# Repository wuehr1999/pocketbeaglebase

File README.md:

# pocketbeaglebase

Add lots of useful features to Your PocketBeagle.

## Features

* Input voltage range: 5 - 28V
* 10/100 Base-T/TX ethernet interface
* 2 USB 2.0 connectors
* RS-232 interface
* CAN interface
* Qwiic connectors: 2 x UART, PRU1 UART, ISC1
* SPI header
* GPIO header

## Connectors

### SPI1 header (P8)

| Pin | Function |
|-----|----------|
| 1 | MISO |
| 2 | 3V3 |
| 3 | SCK |
| 4 | MOSI |
| 5 | CS |
| 6 | GND |

### GPIO header (P4)

| Pin | Function |
|-----|----------|
| 1 | AIN7 |
| 2 | AIN5 |
| 3 | PRU0.5 |
| 4 | IO45 |
| 5 | PRU0.3 |
| 6 | PRU0.2 |
| 7 | IO48 |
| 8 | PRU0.6 |
| 9 | IO64 |
| 10 | IO46 |
| 11 | IO65 |
| 12 | IO27 |
| 13 | IO52 |
| 14 | IO47 |
| 15 | IO60 |
| 16 | IO57 |
| 17 | IO58 |
| 18 | IO23 |
| 19 | IO59 |
| 20 | PWM0A |
| 21 | PWM0B |
| 22 | 3V3 |
| 23 | PRU1.10 |
| 24 | IO26 |
| 25 | PRU0.1 |
| 26 | PRU0.4 |
| 27 | PRU0.7 |
| 28 | AIN4 |
| 29 | NC |
| 30 | AIN3 |
| 31 | NC |
| 32 | AIN2 |
| 33 | AIN1 |
| 34 | IO20 |
| 35 | AIN0 | 
| 36 | VRef+ |
| 37 | VRef- |
| 38 | IO89 |
| 39 | AIN6 |
| 40 | GND |

### RS-232 (UART 0)

| Pin | Function |
|-----|----------|
| 1 | TX |
| 2 | RX |
| 3 | GND |

### CAN (CAN 0)

| Pin | Function |
|-----|----------|
| 1 | CANH |
| 2 | CANL |
| 3 | GND |

The termination can be enabled by closing solder jumper P9 on the bottom of the board.

### UART2, UART4, UARTPRU1 over Qwiic (P3, P5, P6)

| Pin | Function |
|-----|----------|
| 1 | GND |
| 2 | 3v3 |
| 3 | TX |
| 4 | RX |

### I2C1 over Qwiic (P7)

| Pin | Function |
|-----|----------|
| 1 | GND |
| 2 | 3v3 |
| 3 | SDA |
| 4 | SCL |

## PCB

### Toplayer

### Bottomlayer

## Resources

### Manuals

* PocketBeagle System Reference Manual: https://github.com/beagleboard/pocketbeagle/wiki/System-Reference-Manual
* BeagleBone PRU Cookbook: http://beagleboard.org/static/prucookbook/

### Datasheets

* http://ww1.microchip.com/downloads/en/devicedoc/00002306a.pdf
* https://octavosystems.com/docs/osd335x-sm-datasheet/
* https://www.ti.com/lit/ds/symlink/sn65hvd230.pdf?HQS=dis-dk-null-digikeymode-dsf-pf-null-wwe&ts=1609524456800
* https://datasheets.maximintegrated.com/en/ds/MAX3224-MAX3245.pdf
* https://www.ti.com/lit/ds/symlink/tps54335-2a.pdf?ts=1609516162103&ref_url=https%253A%252F%252Fwww.google.com%252F
* http://ww1.microchip.com/downloads/en/devicedoc/21712b.pdf
* https://cdn-reichelt.de/documents/datenblatt/C100/M100_T1D_33E4G_DB_DE.pdf

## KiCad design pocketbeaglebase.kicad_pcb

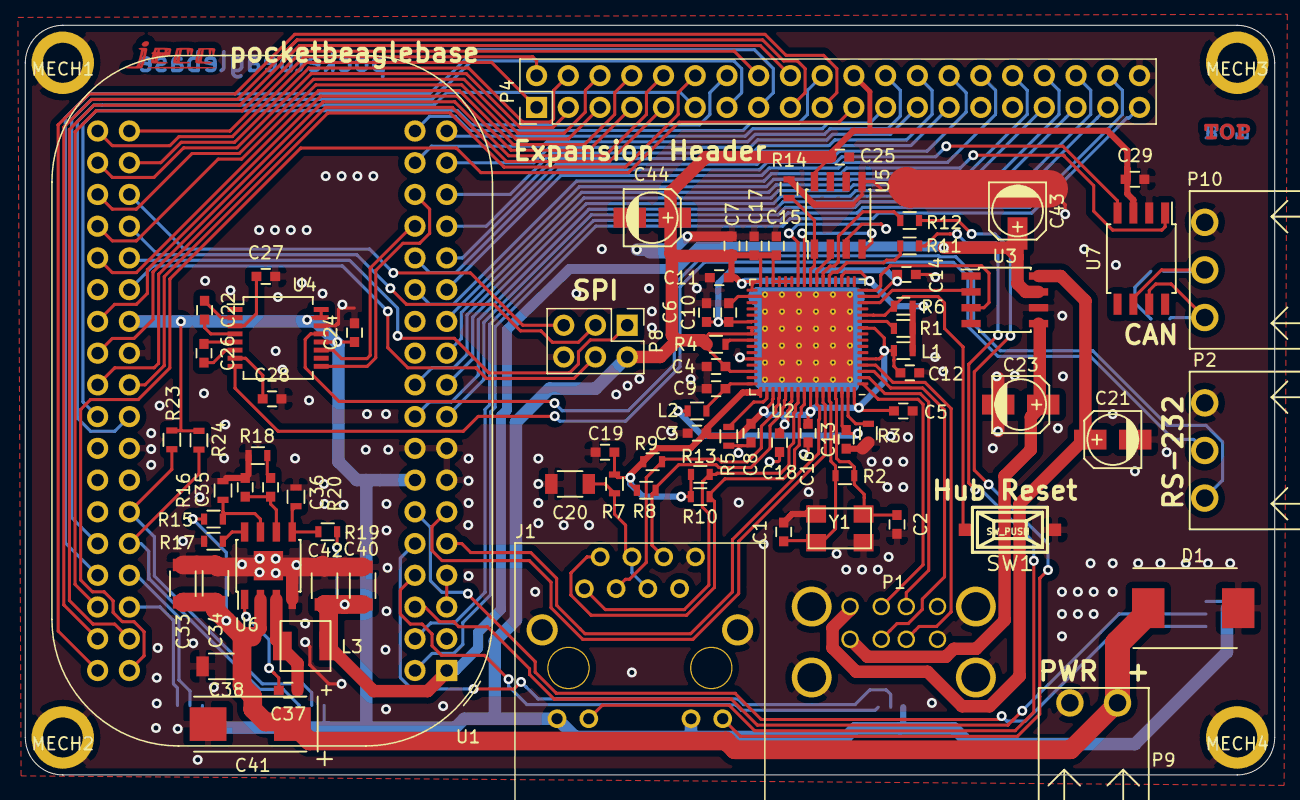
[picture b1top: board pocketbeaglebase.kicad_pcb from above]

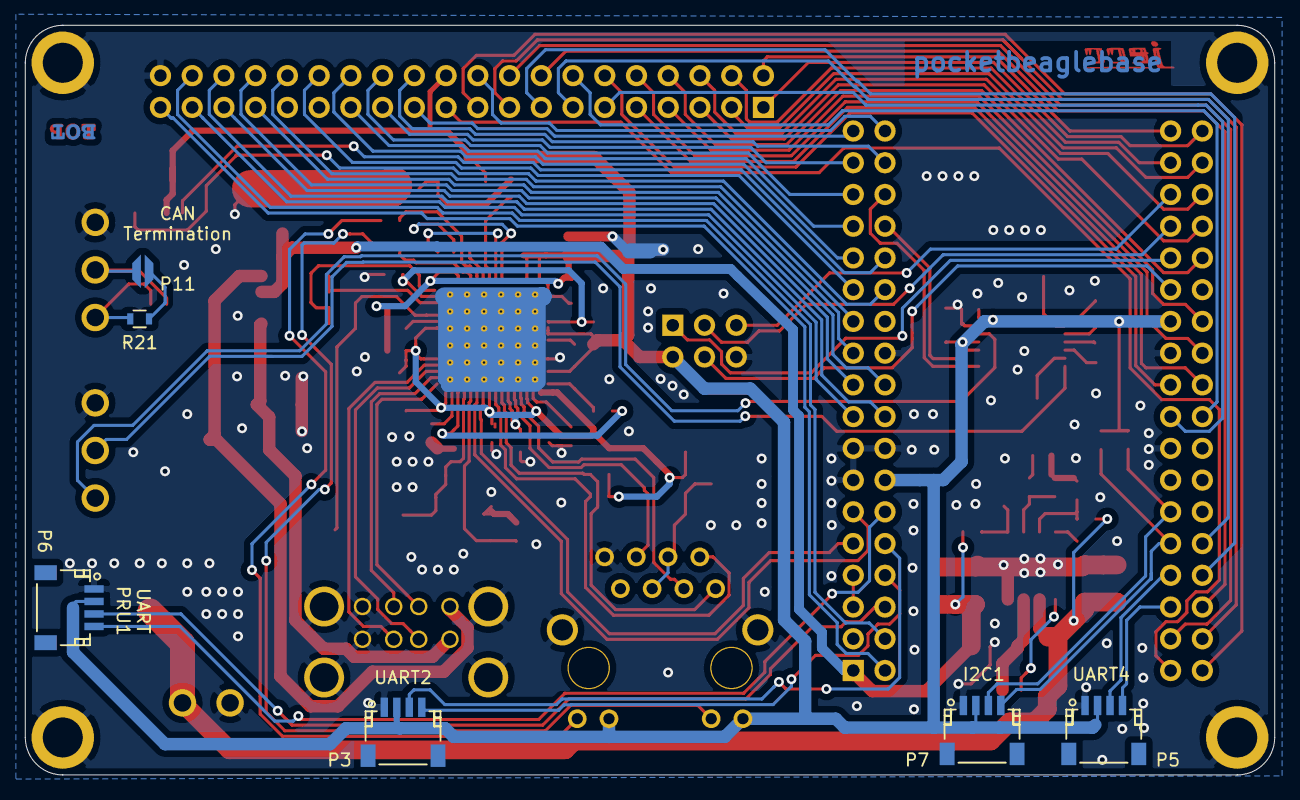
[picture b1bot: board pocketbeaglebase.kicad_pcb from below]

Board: 2 copper layers, 100.0 x 60.0 mm, 95 parts (6 on the bottom side), 109 nets.

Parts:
C1, C2: 330pF; C_0603
C3, C4, C5, C7, C8, C10, C11, C12, C14, C15, C16, C17, C18, C19, C25, C29, C37: 100nF; C_0603
C6: 4.7uF; C_0603
C9, C13, C26, C27, C28: 1uF; C_0603
C20: 22nF; C_1206
C21, C23, C43, C44: 10uF; c_elec_4x4.5
C22, C24: 220nF; C_0603
C33, C34: 4.7uF 50V; C_1206
C35: 120pF; C_0603
C36: 12nF; C_0603
C38: 100nF; C_1206
C40, C42: 22uF; C_1206
C41: 47uF; TantalC_SizeD_EIA-7343_Wave
D1: TVS; DO-214AB
J1: RJ45-TRANSFO-2; RJ_45_TRANSFO_2
L1, L2: 742792651; R_0603
L3: 74437324150; WE-LHMI40xx
L4: Label; jecc_logo_7.2x2.2
L5: Label; Bot
L6: Label; Top
MECH1, MECH2, MECH3, MECH4: MHP_3.2_5.0
P1: USB_2.0_Connector; WE-61400826021
P2, P10: CONN_01X03; WR-TBL_691322310003
P3, P5, P6, P7: CONN_01X04; Connectors_JST_SM04B-SRSS-TB
P4: CONN_02X20; PinHeader_2x20_P2.54mm_Vertical
P8: CONN_02X03; PinHeader_2x03_P2.54mm_Vertical
P9: WR-TBL_691322310002
P11: CONN_01X02; SolderJumper_2mm
R1, R4, R6, R14, R23, R24: 10k; R_0603
R2: 1M; R_0603
R3: 12k; R_0603
R5: 12.4k; R_0603
R7: 10; R_0603
R8, R9, R10, R13: 49.9; R_0603
R11, R12: 220; R_0603
R15: 220k; R_0603
R16: 43.2k; R_0603
R17: 143k; R_0603
R18: 3.74k; R_0603
R19: 100k; R_0603
R20: 19.1k; R_0603
R21: 120R; R_0603
SW1: SW_PUSH; smd_push
U1: BEAGLE_PocketBeagle
U2: LAN9514; QFN-64-1EP_9x9mm_P0.5mm_EP7.3x7.3mm_ThermalVias
U3: MIC2026; SOIC-8_3.9x4.9mm_Pitch1.27mm
U4: MAX3227; SSOP-16_5.3x6.2mm_Pitch0.65mm
U5: 93LC66; SOIC-8_3.9x4.9mm_Pitch1.27mm
U6: TPS54335A; SOIC-8-1EP_3.9x4.9mm_Pitch1.27mm
U7: SN65HVD232; SOIJ-8_5.3x5.3mm_Pitch1.27mm
Y1: 25MHz; Crystal_SMD_5x3.2mm_4Pad

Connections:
+3V3: C4.1, C7.1, C11.1, C15.1, C17.1, C24.1, C25.1, C29.1, C44.1, J1.11, J1.13, L1.1, P3.2, P4.22, P5.2, P6.2, P7.2, P8.2, R1.2, R4.1, R6.2, R23.1, R24.1, U1.14, U1.59, U2.19, U2.27, U2.28, U2.29, U2.30, U2.32, U2.33, U2.39, U2.40, U2.46, U4.12, U4.15, U4.16, U5.8, U7.3
+3V3_S0: C3.1, C5.1, C8.1, C12.1, C16.1, C18.1, C19.1, L1.2, R7.1, R8.1, R9.1, R10.1, R13.1, U2.5, U2.10, U2.49, U2.51, U2.54, U2.57, U2.64
+5V: C40.1, C42.1, C43.1, L3.2, R19.1, U1.1, U3.7
+BATT: C33.1, C34.1, C38.1, C41.1, D1.1, P9.2, R15.1, U6.2
/LAN9514/n18: C6.1, C10.1, C14.1, U2.15, U2.38
/LAN9514/n18ETH: C9.1, L2.1, U2.48
/LAN9514/n18USB: C13.1, L2.2, U2.62
/LAN9514/nEECLK: U2.23, U5.2
/LAN9514/nEECS: R14.1, U2.24, U5.1
/LAN9514/nEEDI: U2.26, U5.3
/LAN9514/nEEDO: U2.25, U5.4
/LAN9514/nPRTCTL2: U2.14, U3.1, U3.2
/LAN9514/nPRTCTL3: U2.16, U3.3, U3.4
/LAN9514/nPWR2: C21.1, P1.1, U3.8
/LAN9514/nPWR3: C23.1, P1.5, U3.5
/LAN9514/nRXN: J1.6, R8.2, U2.53
/LAN9514/nRXP: J1.3, R9.2, U2.52
/LAN9514/nTXN: J1.2, R10.2, U2.56
/LAN9514/nTXP: J1.1, R13.2, U2.55
/LAN9514/nUSBDM2: P1.2, U2.1
/LAN9514/nUSBDM3: P1.6, U2.3
/LAN9514/nUSBDP2: P1.3, U2.2
/LAN9514/nUSBDP3: P1.7, U2.4
/LAN9514/~nLNKA_LED: R11.1, U2.21
/LAN9514/~nSPD_LED: R12.1, U2.22
/UART/nCANH: P10.1, R21.2, U7.7
/UART/nCANL: P10.2, P11.2, U7.6
/nA0: P4.35, U1.19
/nA1: P4.33, U1.21
/nA2: P4.32, U1.23
/nA3: P4.30, U1.25
/nA4: P4.28, U1.27
/nA5: P4.2, U1.71
/nA6: P4.39, U1.2
/nA7: P4.1, U1.72
/nIO20: P4.34, U1.20
/nIO23: P4.18, U1.39
/nIO26: P4.24, U1.34
/nIO27: P4.12, U1.55
/nIO45: P4.4, U1.69
/nIO46: P4.10, U1.58
/nIO47: P4.14, U1.54
/nIO48: P4.7, U1.60
/nIO52: P4.13, U1.46
/nIO57: P4.16, U1.42
/nIO58: P4.17, U1.40
/nIO59: P4.19, U1.38
/nIO60: P4.15, U1.44
/nIO64: P4.9, U1.56
/nIO65: P4.11, U1.53
/nIO89: P4.38, U1.4
/nPRU0.1: P4.25, U1.33
/nPRU0.2: P4.6, U1.68
/nPRU0.3: P4.5, U1.66
/nPRU0.4: P4.26, U1.31
/nPRU0.5: P4.3, U1.70
/nPRU0.6: P4.8, U1.64
/nPRU0.7: P4.27, U1.29
/nPRU1.10: P4.23, U1.35
/nPWM0A: P4.20, U1.36
/nPWM0B: P4.21, U1.37
/nVREF+: P4.36, U1.18
/nVREF-: P4.37, U1.17
/power/COMP: C35.1, C36.1, U6.6
/power/EN: R15.2, R16.1, U6.7
/power/PH: C37.1, L3.1, U6.3
/power/RT: R17.1, U6.8
/power/SENSE5V: R19.2, R20.1, U6.5
CAN0_RX: U1.28, U7.4
CAN0_TX: U1.26, U7.1
CS: P8.5, U1.67
GND: C1.2, C2.2, C3.2, C4.2, C5.2, C6.2, C7.2, C8.2, C9.2, C10.2, C11.2, C12.2, C13.2, C14.2, C15.2, C16.2, C17.2, C18.2, C19.2, C20.2, C21.2, C23.2, C24.2, C25.2, C27.2, C28.2, C29.2, C33.2, C34.2, C35.2, C38.2, C40.2, C41.2, C42.2, C43.2, C44.2, D1.2, J1.8, J1.SH, MECH1.1, MECH2.1, MECH3.1, MECH4.1, P1.4, P1.8, P1.M1, P1.M2, P1.M3, P1.M4, P2.3, P3.1, P4.40, P5.1, P6.1, P7.1, P8.6, P9.1, P10.3, R3.2, R5.2, R14.2, R16.2, R17.2, R18.2, R20.2, SW1.1, U1.13, U1.15, U1.16, U1.22, U1.51, U1.57, U2.34, U2.44, U2.65, U3.6, U4.14, U5.5, U6.4, U6.9, U7.2, Y1.2, Y1.4
MISO: P8.1, U1.63
MOSI: P8.4, U1.61
unnamed: C1.1, R2.2, U2.60, Y1.1
unnamed: C2.1, R2.1, U2.61, Y1.3
unnamed: C20.1, J1.4, J1.5, R7.2
unnamed: C22.1, U4.2
unnamed: C22.2, U4.4
unnamed: C26.1, U4.5
unnamed: C26.2, U4.6
unnamed: C27.1, U4.3
unnamed: C28.1, U4.7
unnamed: C36.2, R18.1
unnamed: C37.2, U6.1
unnamed: J1.12, R11.2
unnamed: J1.14, R12.2
unnamed: P2.1, U4.13
unnamed: P2.2, U4.8
unnamed: P11.1, R21.1
unnamed: R1.1, U2.11
unnamed: R3.1, U2.63
unnamed: R4.2, U2.41
unnamed: R5.1, U2.50
unnamed: R6.1, SW1.2, U2.12
PR1_RX: P6.4, U1.12
PR1_TX: P6.3, U1.6
RX0: U1.32, U4.9
RX2: P3.4, U1.8
RX4: P5.4, U1.41
SCK: P8.3, U1.65
SCL1: P7.4, R24.2, U1.45
SDA1: P7.3, R23.2, U1.47
TX0: U1.30, U4.11
TX2: P3.3, U1.10
TX4: P5.3, U1.43
USB_DM: U1.9, U2.58
USB_DP: U1.11, U2.59
USB_VBUS: U1.5, U1.7

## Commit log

2020-12-10 added current state
2020-12-11 review and discussion done
2020-12-11 added can bus
2020-12-12 somehow done with general layouting
2020-12-13 finally
2021-01-01 tested and fixed last bugs
2021-01-01 Create LICENSE
